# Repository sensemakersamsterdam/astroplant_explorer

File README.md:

# astroplant_explorer

SensemakersAms is working on additional stuff for the Astroplant.io project. This repository is meant to cooperate on these extensions without messing up the official project. As soon we have things that are ready to be used by a much larger audience, they will be moved to the main repository https://github.com/AstroPlant 

For documentation of the main project see: https://astroplant.gitbook.io/join-mission/

For documentation of this explorer project / kit, we made a wiki: https://github.com/sensemakersamsterdam/astroplant_explorer/wiki

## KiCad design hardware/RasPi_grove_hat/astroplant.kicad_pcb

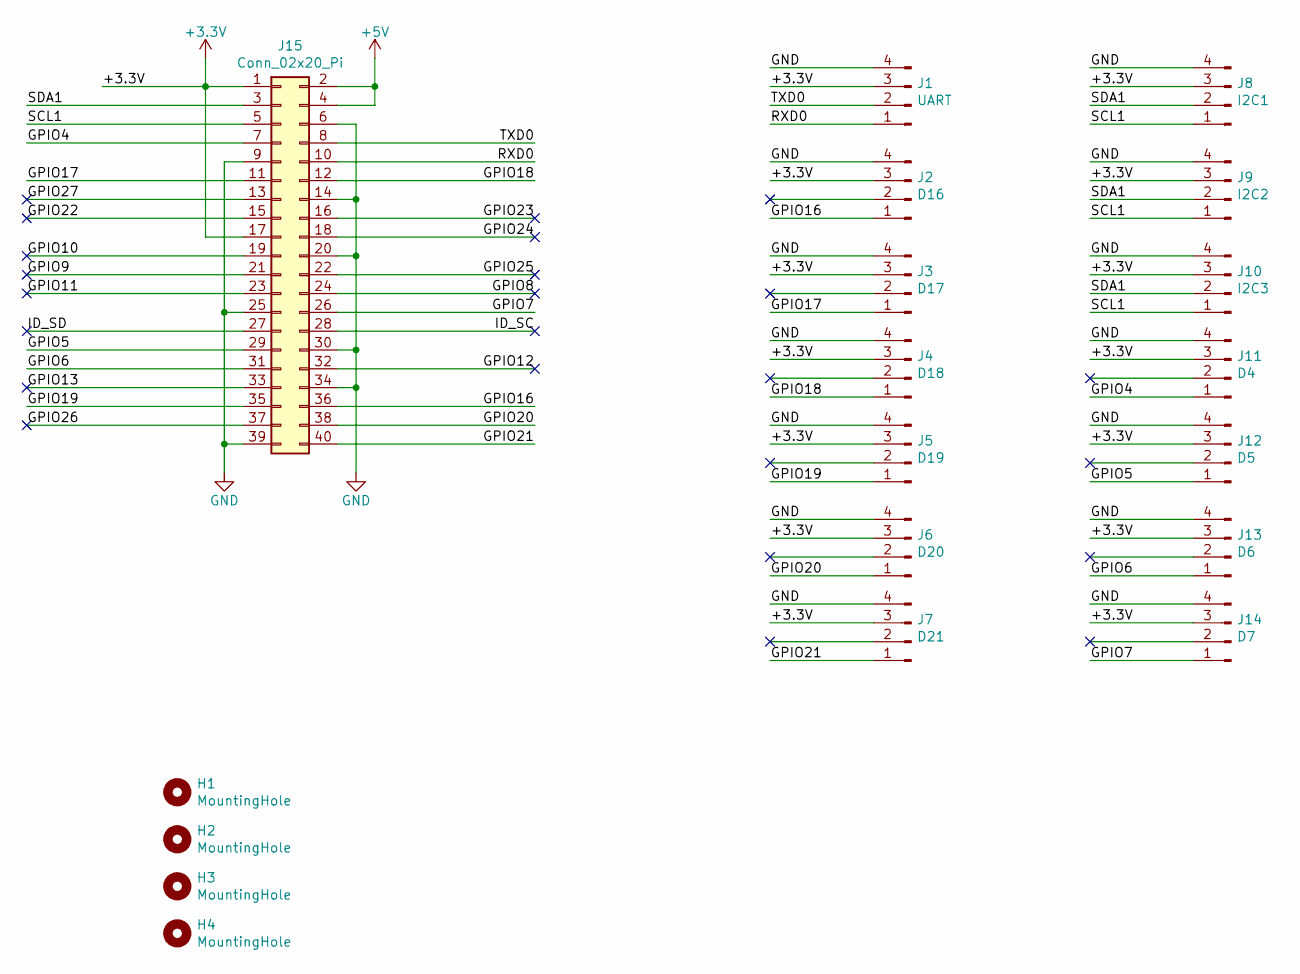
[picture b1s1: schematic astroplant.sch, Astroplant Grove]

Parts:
H1, H2, H3, H4: MountingHole; MountingHole_2.7mm
J1: UART; JST_PH_B4B-PH-K_1x04_P2.00mm_Vertical
J2: D16; JST_PH_B4B-PH-K_1x04_P2.00mm_Vertical
J3: D17; JST_PH_B4B-PH-K_1x04_P2.00mm_Vertical
J4: D18; JST_PH_B4B-PH-K_1x04_P2.00mm_Vertical
J5: D19; JST_PH_B4B-PH-K_1x04_P2.00mm_Vertical
J6: D20; JST_PH_B4B-PH-K_1x04_P2.00mm_Vertical
J7: D21; JST_PH_B4B-PH-K_1x04_P2.00mm_Vertical
J8: I2C1; JST_PH_B4B-PH-K_1x04_P2.00mm_Vertical
J9: I2C2; JST_PH_B4B-PH-K_1x04_P2.00mm_Vertical
J10: I2C3; JST_PH_B4B-PH-K_1x04_P2.00mm_Vertical
J11: D4; JST_PH_B4B-PH-K_1x04_P2.00mm_Vertical
J12: D5; JST_PH_B4B-PH-K_1x04_P2.00mm_Vertical
J13: D6; JST_PH_B4B-PH-K_1x04_P2.00mm_Vertical
J14: D7; JST_PH_B4B-PH-K_1x04_P2.00mm_Vertical
J15: Conn_02x20_Pi; PinSocket_2x20_P2.54mm_Vertical

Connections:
+3V3: J1.3, J2.3, J3.3, J4.3, J5.3, J6.3, J7.3, J8.3, J9.3, J10.3, J11.3, J12.3, J13.3, J14.3, J15.1, J15.17
+5V: J15.2, J15.4
/GPIO4: J11.1, J15.7
/GPIO5: J12.1, J15.29
/GPIO6: J13.1, J15.31
/GPIO7: J14.1, J15.26
/GPIO8: J15.24
/GPIO9: J15.21
/GPIO10: J15.19
/GPIO11: J15.23
/GPIO12: J15.32
/GPIO13: J15.33
/GPIO16: J2.1, J15.36
/GPIO17: J3.1, J15.11
/GPIO18: J4.1, J15.12
/GPIO19: J5.1, J15.35
/GPIO20: J6.1, J15.38
/GPIO21: J7.1, J15.40
/GPIO22: J15.15
/GPIO23: J15.16
/GPIO24: J15.18
/GPIO25: J15.22
/GPIO26: J15.37
/GPIO27: J15.13
/ID_SC: J15.28
/ID_SD: J15.27
/RXD0: J1.1, J15.10
/SCL1: J8.1, J9.1, J10.1, J15.5
/SDA1: J8.2, J9.2, J10.2, J15.3
/TXD0: J1.2, J15.8
GND: J1.4, J2.4, J3.4, J4.4, J5.4, J6.4, J7.4, J8.4, J9.4, J10.4, J11.4, J12.4, J13.4, J14.4, J15.6, J15.9, J15.14, J15.20, J15.25, J15.30, J15.34, J15.39

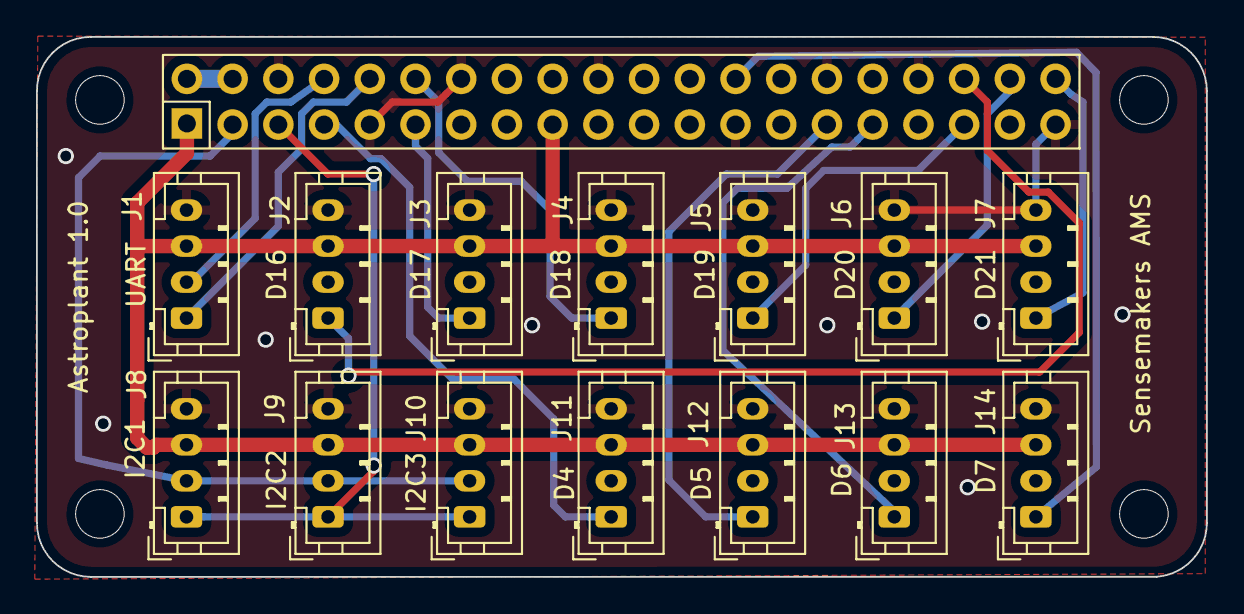
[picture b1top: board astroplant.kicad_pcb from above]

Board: 2 copper layers, 65.0 x 30.0 mm, 19 parts (0 on the bottom side), 17 nets.

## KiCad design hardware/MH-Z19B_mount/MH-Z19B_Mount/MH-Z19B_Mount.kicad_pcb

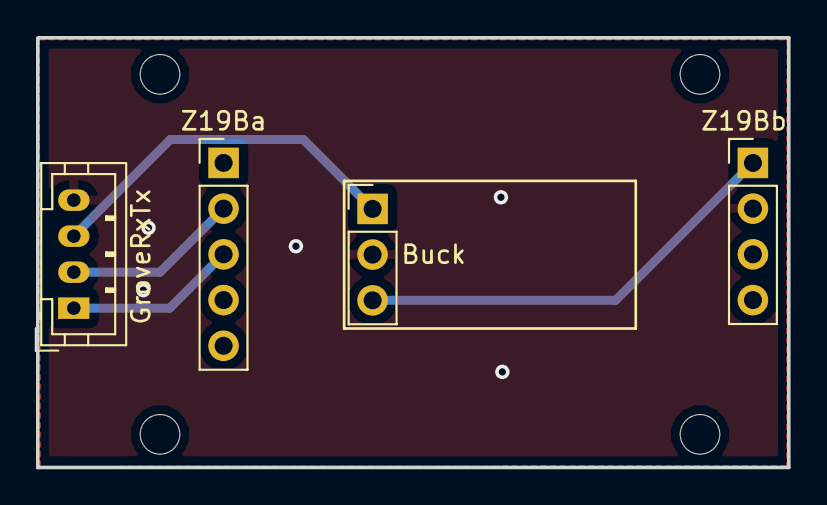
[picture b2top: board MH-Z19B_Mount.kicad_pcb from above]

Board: 2 copper layers, 41.7 x 23.9 mm, 8 parts (0 on the bottom side), 5 nets.

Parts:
Buck: Buck; PinHeader_1x03_P2.54mm_Vertical
GroveRxTx: GroveSer; JST_PH_B4B-PH-K_1x04_P2.00mm_Vertical
MH1, MH2, MH3, MH4: MountingHole; MountingHole_2.2mm_M2
Z19Ba: Z19B-C1; PinHeader_1x05_P2.54mm_Vertical
Z19Bb: Z19B-C2; PinHeader_1x04_P2.54mm_Vertical

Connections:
/Gnd: Buck.2, GroveRxTx.4, Z19Bb.2
/RxTx: GroveRxTx.2, Z19Ba.2
/TxRx: GroveRxTx.1, Z19Ba.3
/V3.3: Buck.1, GroveRxTx.3
/V5: Buck.3, Z19Bb.1

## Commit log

2019-09-12 initial readme
2019-09-12 Create explorerboard.svg
    design for base to be laser cut
2019-09-12 python scripts block 1
2019-09-15 image for wiki
2019-10-05 added fading grow led image
2019-10-05 upload animated fading grow led
2019-10-14 relay.py
2019-10-14 Rename block3 to relay.py
2019-10-20 added first block 4 scripts
2019-11-12 Create relay.py
    Dit is het standaard script voor een relay.
2019-11-12 Script controls LED and fan based on temperature
    Extended version of waterTemp.py to control a LED and a (Grove) relay.
2019-11-12 shutdown_button.py
    This scripts shutdowns the pi after pushing button #3 longer than 5 s
2019-11-13 Update showIP.py
    script werkend gekregen door time.sleep(60) toe te voegen voor het ip adres wordt opgevraagd.
2019-11-15 5 files for creating csv with sensor readings
    csv_writer is the main file to write the csv. It uses sensor data from the 4 other scripts
2019-11-17 added images for block 3
2019-11-23 adapted_lcdi2c_module
    adapted from sensor test script to module to be called from other scripts (like read_all.py)
2019-11-24 Update read_all.py
    added loop
2019-11-24 Create read_all.service
    service to automatically start read_all.py at boot
2019-11-27 Create simple_light.py
    first step to script to control the LED lights
2019-11-27 Update simple_light.py
    added comment
2019-11-29 Update simple_light.py
    learning about branches
2019-11-29 added code to show IP address
2019-11-29 block 1 cleanup
2019-11-29 added pwm
2019-11-29 Create timed_light.py
    changes LED values according to time scheme
2019-11-29 cleanup
2019-11-30 Create actuator_control.py
    script to control leds and fans (hard coded)
2019-11-30 Create actuator_control2.py
    script to control leds and fans with json light recipe
2019-11-30 initial code
2019-11-30 better __init__.py
2019-12-01 plaatje werking read_all.jpg
2019-12-01 expanded drivers and demos
2019-12-01 ip utils added, lcd driver added, simple show_ip_address added
2019-12-02 configuration module and local mqtt module added
2019-12-02 checkpoint
2019-12-02 random bug fixes
2019-12-03 2 modules main program
2019-12-04 Added README.md with prerequisites and set-up instructions
2019-12-04 directory structure reorganised
2019-12-04 first setup axa_display
2019-12-05 Update read_all2.py
    added comments
2019-12-05 picture for the wiki
2019-12-05 renamed new_implementation to advanced
2019-12-05 directories in advanced renamed
2019-12-07 restructure part 1
2019-12-07 restructure part 2
2019-12-07 renamed basic_demos to learning_stuff
2019-12-07 renamed floders in learning stuff
2019-12-07 renamed actuator control script
2019-12-07 added sensor test scripts
2019-12-07 fixed some errors
2019-12-08 corrected name
2019-12-08 Rename read__and_write_all.service to read_and_write_all.service
2019-12-08 fixed bug
2019-12-08 CAble dct design files added
2019-12-08 RasPi Grove hat added
2019-12-08 sleep toegevoegd
2019-12-09 better comment
2019-12-09 mqtt demo 1 comments
2019-12-10 bug gettimg ip address fixed
2019-12-10 Create README.md with 3D print instructions.
2019-12-11 duct picts added
2019-12-12 Loads of comments added
2019-12-22 added eTape.py
2019-12-24 added from time import sleep
2019-12-24 fixed typo
2019-12-24 added a button sender and led receiver with the demo
2019-12-25 added mqtt demo 2
2020-01-01 Create green_pixels
    This scripts counts the number of green pixels in a given image.
2020-01-01 basilicum to use with pixel count script
2020-02-10 Kicad files for RasPi hat added
2020-02-15 changed name light_1x.py to bh1750.py
2020-02-15 changed file names -1x.py
2020-02-15 added mqtt reconnect and logging
2020-02-15 Update DHT22.py
    cleaned code a bit and added comments
2020-02-15 Update bh1750.py
    changed name light_x1.py into bh1750.py
2020-03-24 Wallpapers for Download
2020-03-24 added wallpaper directory
2020-03-28 improved indentation
2020-03-28 changed return value to number instead of dict
2020-03-28 added main function
2020-03-28 added display function for convenience
2020-03-28 clean up
    simplified directory structure learning stuff
2020-03-28 clean up
    moved scripts learning_stuff together
2020-03-28 clean up
    made directory miscellaneous for older experimental stuff
2020-03-28 adapted service for read and send all
2020-03-28 changed MQTT topic and app.id in astroplant
2020-03-28 added script for bme280
2020-03-28 added script to upload images to minio
2020-03-29 added support for bme280
2020-03-29 clean up
    changed name actuator_control_from_light_recipe.py to LED_control_from_light_recipe.py and moved eTape.py to miscellaneous
2020-04-23 hardware additions and .gitignore update
2020-04-23 New stuff made during walkthrough
2020-04-24 mhz19b.py improved and beter documented led.py, relay.py and _output.py
2020-04-24 pep formatted some drivers
2020-04-27 added BME280 driver and demo
2020-04-27 added BH1750 driver and demo
2020-04-27 added buzzer driver and demo
2020-04-27 added ds18b20 driver and demo
2020-04-27 updated bme280 driver and demo
2020-04-28 - Changed ae_drivers.bme280: - is now a singleton class - bug in reading calibration data removed - reformatted - allowed specification of an external smb/i2c-bus - added a test in set-up if the bme2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
2020-04-29 Cleaned up mhz19b driver and demo (#20)
    * Testing git functionality
    * Delete testing_TJ.py
    * Cleaned up mhz19b demo and driver
2020-04-29 updated ds18b20 driver
2020-05-05 added mqtt_light_scheduler and light_recipe
2020-05-05 added timelapse stuff
2020-05-08 fixed time_lapse_control.py
2020-05-12 tijdelijke .json geupload tbv notebook
2020-05-19 lcd work in progress
2020-05-20 Display program - first working version
2020-05-20 axe_display bug fix
